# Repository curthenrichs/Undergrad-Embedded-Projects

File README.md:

# Undergrad-Embedded-Projects
Some notable coursework projects from my time in undergrad. Provided here mainly for reference.

- [CE 3910 - Embedded Systems III - Tracking Turret](./CE3910-Embedded-Systems-III/nios/README.md)
- [CE 3910 - Embedded Systems III - PCB](./CE3910-Embedded-Systems-III/PCB_Design/README.md)
- [CE 4920 - Embedded Systems IV](./CE4920-Embedded-Systems-IV/README.md)
- [CE 4950 - Networking One](./CE4950-Networking-One/README.md)

Unfortunately these project are not well (externally) documented at this time. These
projects are provided for code reference if desired.

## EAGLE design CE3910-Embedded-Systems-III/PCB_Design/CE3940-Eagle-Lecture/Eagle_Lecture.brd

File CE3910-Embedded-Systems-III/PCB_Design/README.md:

# CE 3910 Embedded Systems III - Eagle PCB Layout

Simple microcontroller breakout board designed in Eagle based off a lecture given
in embedded systems III.

## Design
Please refer to `PCB_Design\CE3940-Eagle-Lecture` for design submitted in the course.

This is project is for archival and reference purposes. Design is not maintained.

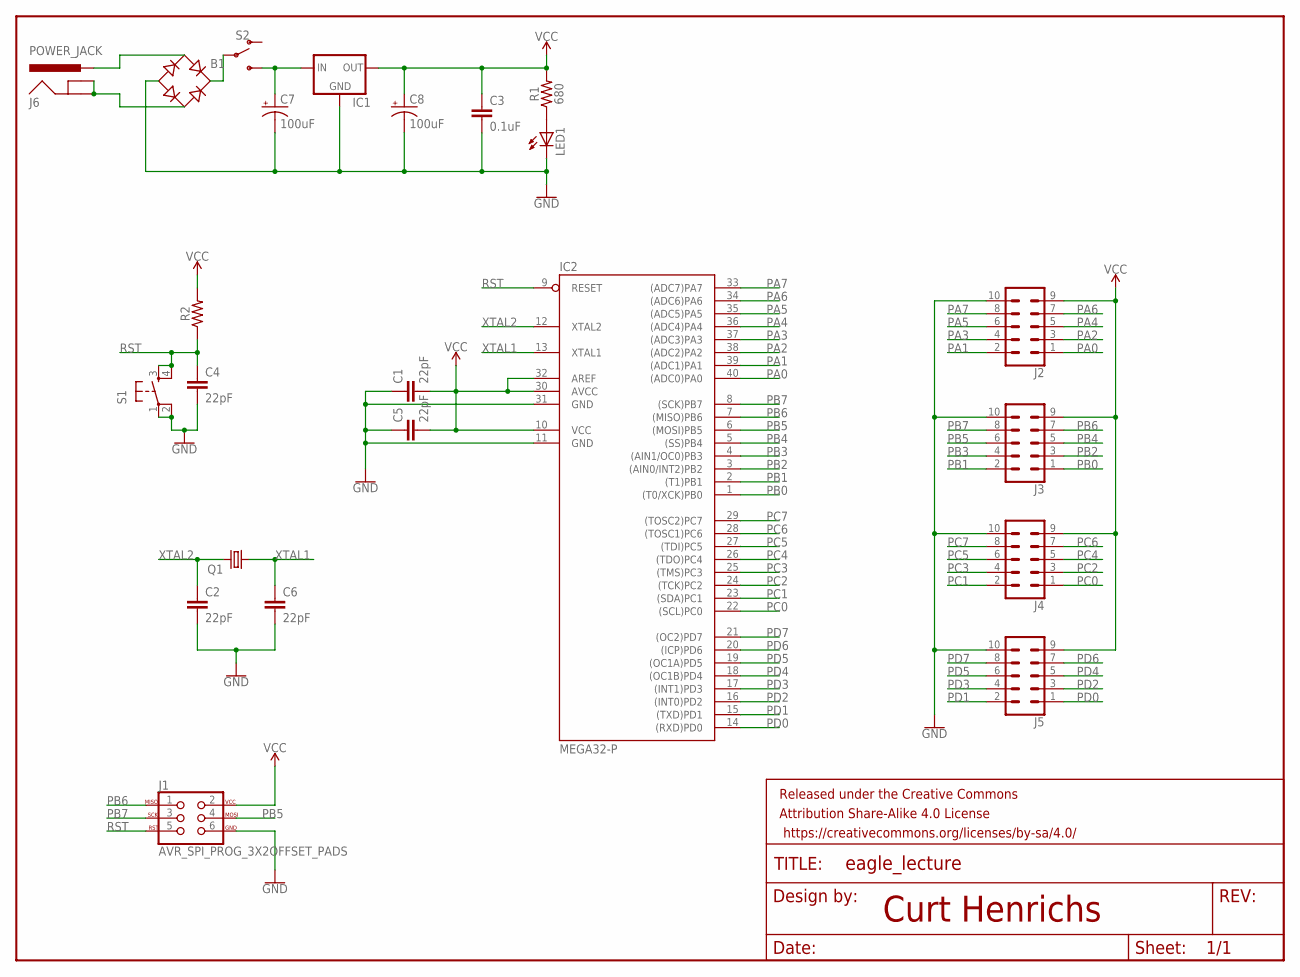
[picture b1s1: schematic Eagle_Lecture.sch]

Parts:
B1: B-DIL
C1, C2, C4, C5, C6: 22pF; CAP-PTH-2.54
C3: 0.1uF; CAP-PTH-2.54
C7, C8: 100uF; CPOL-RADIAL-2.5MM-6.5MM
FRAME1: FRAME-LETTER; CREATIVE_COMMONS
IC1: 78MXXL
IC2: MEGA32-P; DIL40
J1: AVR_SPI_PROG_3X2OFFSET_PADS; 2X3_OFFSET
J2, J3, J4, J5: CONN_05X2SHD; 2X5-SHROUDED
J6: POWER_JACK; POWER_JACK_PTH
LED1: LED3MM
Q1: CRYSTALHC49U-V; HC49U-V
R1: 680; AXIAL-0.3
R2: AXIAL-0.3
S1: TAC_SWITCHPTH; TACTILE-PTH
S2: SWITCH-SPDT-PTH-11.6X4.0MM; SWITCH_SPDT_PTH_11.6X4.0MM

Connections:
GND: B1.-, C1.1, C2.2, C3.2, C4.2, C5.1, C6.2, C7.2 (-), C8.2 (-), IC1.GND, IC2.11 (GND), IC2.31 (GND), J1.6, J2.10, J3.10, J4.10, J5.10, LED1.K (C), S1.1, S1.2
unnamed: B1.AC2, J6.GND, J6.GNDBREAK
unnamed: B1.AC1, J6.PWR
unnamed: B1.+, S2.2
unnamed: C7.1 (+), IC1.IN, S2.3 (S)
unnamed: LED1.A, R1.P$1 (1)
PA0: IC2.40 ((ADC0)PA0), J2.1
PA1: IC2.39 ((ADC1)PA1), J2.2
PA2: IC2.38 ((ADC2)PA2), J2.3
PA3: IC2.37 ((ADC3)PA3), J2.4
PA4: IC2.36 ((ADC4)PA4), J2.5
PA5: IC2.35 ((ADC5)PA5), J2.6
PA6: IC2.34 ((ADC6)PA6), J2.7
PA7: IC2.33 ((ADC7)PA7), J2.8
PB0: IC2.1 ((T0/XCK)PB0), J3.1
PB1: IC2.2 ((T1)PB1), J3.2
PB2: IC2.3 ((AIN0/INT2)PB2), J3.3
PB3: IC2.4 ((AIN1/OC0)PB3), J3.4
PB4: IC2.5 ((SS)PB4), J3.5
PB5: IC2.6 ((MOSI)PB5), J1.4, J3.6
PB6: IC2.7 ((MISO)PB6), J1.1, J3.7
PB7: IC2.8 ((SCK)PB7), J1.3, J3.8
PC0: IC2.22 ((SCL)PC0), J4.1
PC1: IC2.23 ((SDA)PC1), J4.2
PC2: IC2.24 ((TCK)PC2), J4.3
PC3: IC2.25 ((TMS)PC3), J4.4
PC4: IC2.26 ((TDO)PC4), J4.5
PC5: IC2.27 ((TDI)PC5), J4.6
PC6: IC2.28 ((TOSC1)PC6), J4.7
PC7: IC2.29 ((TOSC2)PC7), J4.8
PD0: IC2.14 ((RXD)PD0), J5.1
PD1: IC2.15 ((TXD)PD1), J5.2
PD2: IC2.16 ((INT0)PD2), J5.3
PD3: IC2.17 ((INT1)PD3), J5.4
PD4: IC2.18 ((OC1B)PD4), J5.5
PD5: IC2.19 ((OC1A)PD5), J5.6
PD6: IC2.20 ((ICP)PD6), J5.7
PD7: IC2.21 ((OC2)PD7), J5.8
RST: C4.1, IC2.9 (RESET), J1.5, R2.P$1 (1), S1.3, S1.4
VCC: C1.2, C3.1, C5.2, C8.1 (+), IC1.OUT, IC2.10 (VCC), IC2.30 (AVCC), IC2.32 (AREF), J1.2, J2.9, J3.9, J4.9, J5.9, R1.P$2 (2), R2.P$2 (2)
XTAL1: C6.1, IC2.13 (XTAL1), Q1.1
XTAL2: C2.1, IC2.12 (XTAL2), Q1.2

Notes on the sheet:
Curt Henrichs

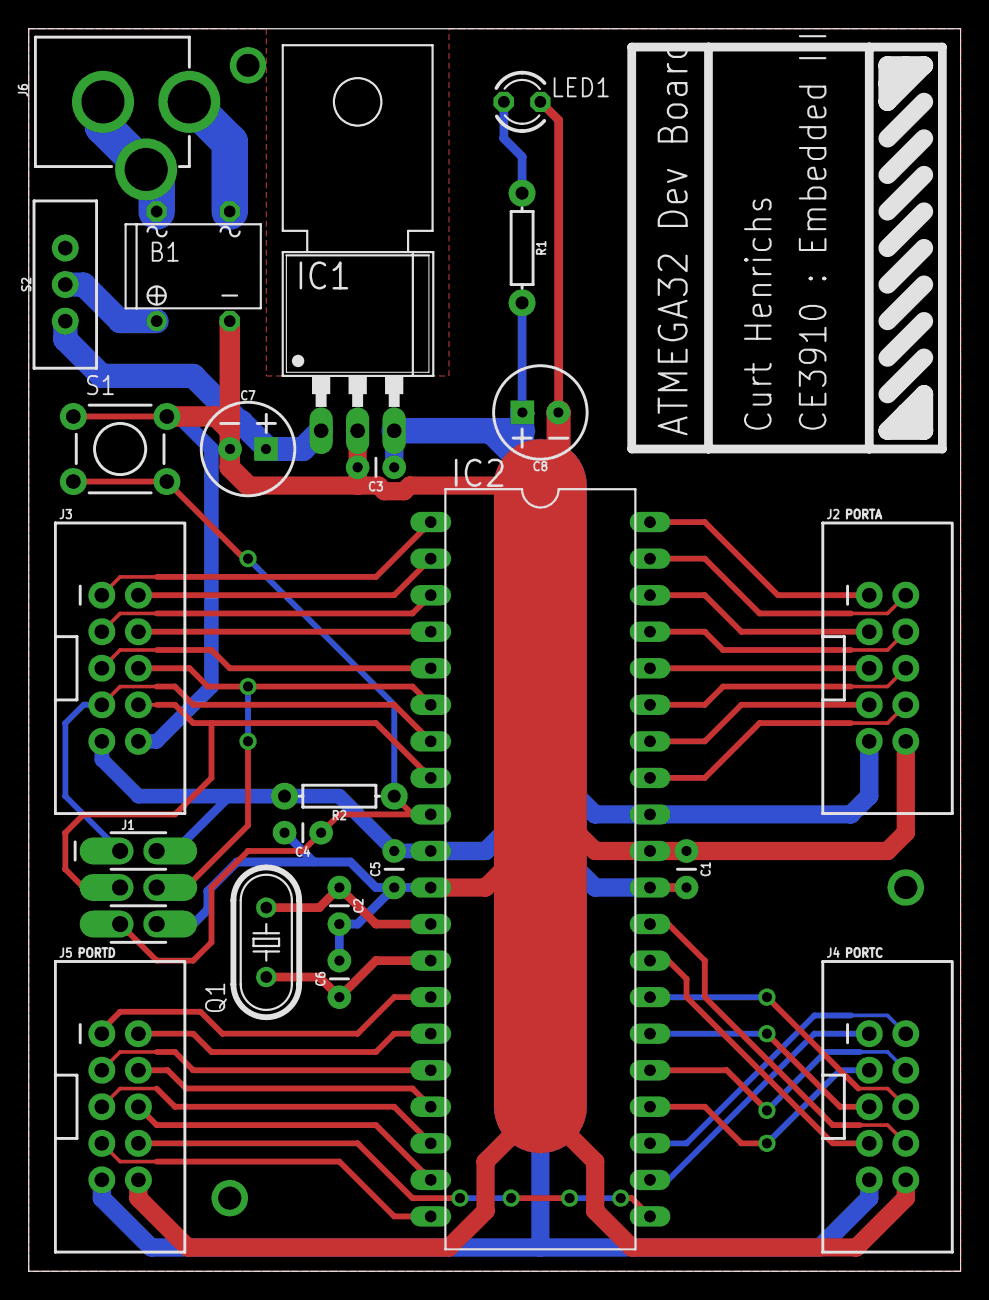
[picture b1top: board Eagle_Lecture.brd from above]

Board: 2 copper layers, 64.8 x 86.4 mm, 24 parts (0 on the bottom side), 42 nets.

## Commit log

2021-04-03 initial commit - copying over project directories
2021-04-04 Working on initial documentation and adding embedded projects themselves
2021-04-06 updating documentation

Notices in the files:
parts and their libraries:
SparkFun-Capacitors: Licensing: Creative Commons ShareAlike 4.0 International - https://creativecommons.org/licenses/by-sa/4.0
SparkFun-Aesthetics: Released under the Creative Commons Attribution Share-Alike 4.0 License
SparkFun-Aesthetics: https://creativecommons.org/licenses/by-sa/4.0
